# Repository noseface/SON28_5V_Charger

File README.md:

In this projekt I try to create a charger, which handles the AC-supply produced by a 'SON28 Dynamo' and transformed it into a stable 5 VDC to charge a phone or powerbank.

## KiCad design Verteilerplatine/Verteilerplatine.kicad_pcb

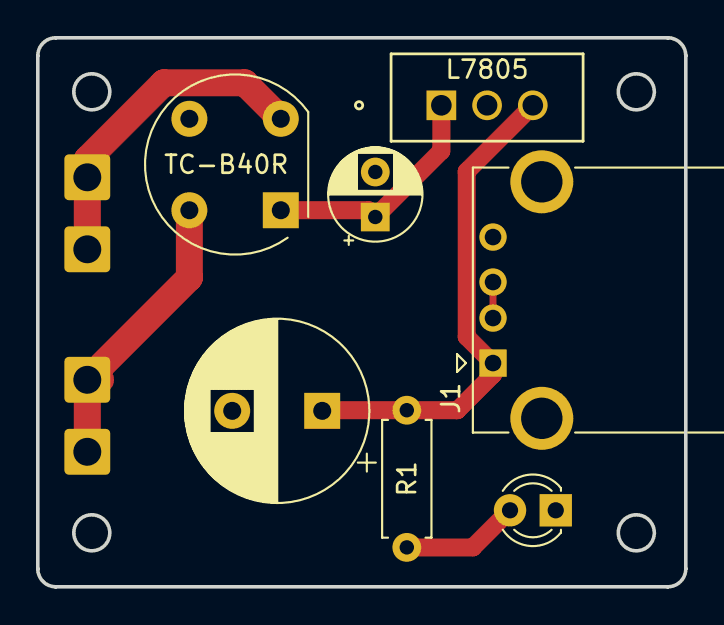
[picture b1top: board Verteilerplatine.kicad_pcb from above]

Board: 2 copper layers, 36.0 x 30.5 mm, 11 parts (0 on the bottom side), 7 nets.

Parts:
Cout1: 1000uF; CP_Radial_D10.0mm_P5.00mm
Cout3: 100uF; CP_Radial_D5.0mm_P2.50mm
D1: LED; LED_D3.0mm_IRBlack
H5, H6, H7, H8: MountingHole_Pad; SolderWire-0.75sqmm_1x01_D1.25mm_OD2.3mm
J1: USB3_A; USB_A_CONNFLY_DS1095-WNR0
L7805: L7805CV; TO-220_STM
R1: 10k; R_Axial_DIN0207_L6.3mm_D2.5mm_P7.62mm_Horizontal
TC-B40R: W01G; Diode_Bridge_Round_D9.8mm

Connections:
5V: Cout1.1, J1.1 (VBUS), L7805.3 (OUTPUT), R1.1
GND: Cout1.2, Cout3.2, D1.1 (K), J1.4 (GND), L7805.2 (GROUND), TC-B40R.3 (-)
unnamed: D1.2 (A), R1.2
unnamed: J1.2 (D-), J1.3 (D+)
U_dm: H6.1, H8.1, TC-B40R.2
U_dp: H5.1, H7.1, TC-B40R.4
U_eff: Cout3.1, L7805.1 (INPUT), TC-B40R.1 (+)

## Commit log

2025-04-15 Prototyp 1
    The circuit does not work above 12 km/h. Currently try to find the mistake and will publish a better version.
2025-04-30 Update and order for pcb (Buck-Converter, Layout)
2025-05-31 New housing for Prototype 2
